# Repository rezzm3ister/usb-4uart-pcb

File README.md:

# usb-4uart-pcb
circuit board for 4x uart board

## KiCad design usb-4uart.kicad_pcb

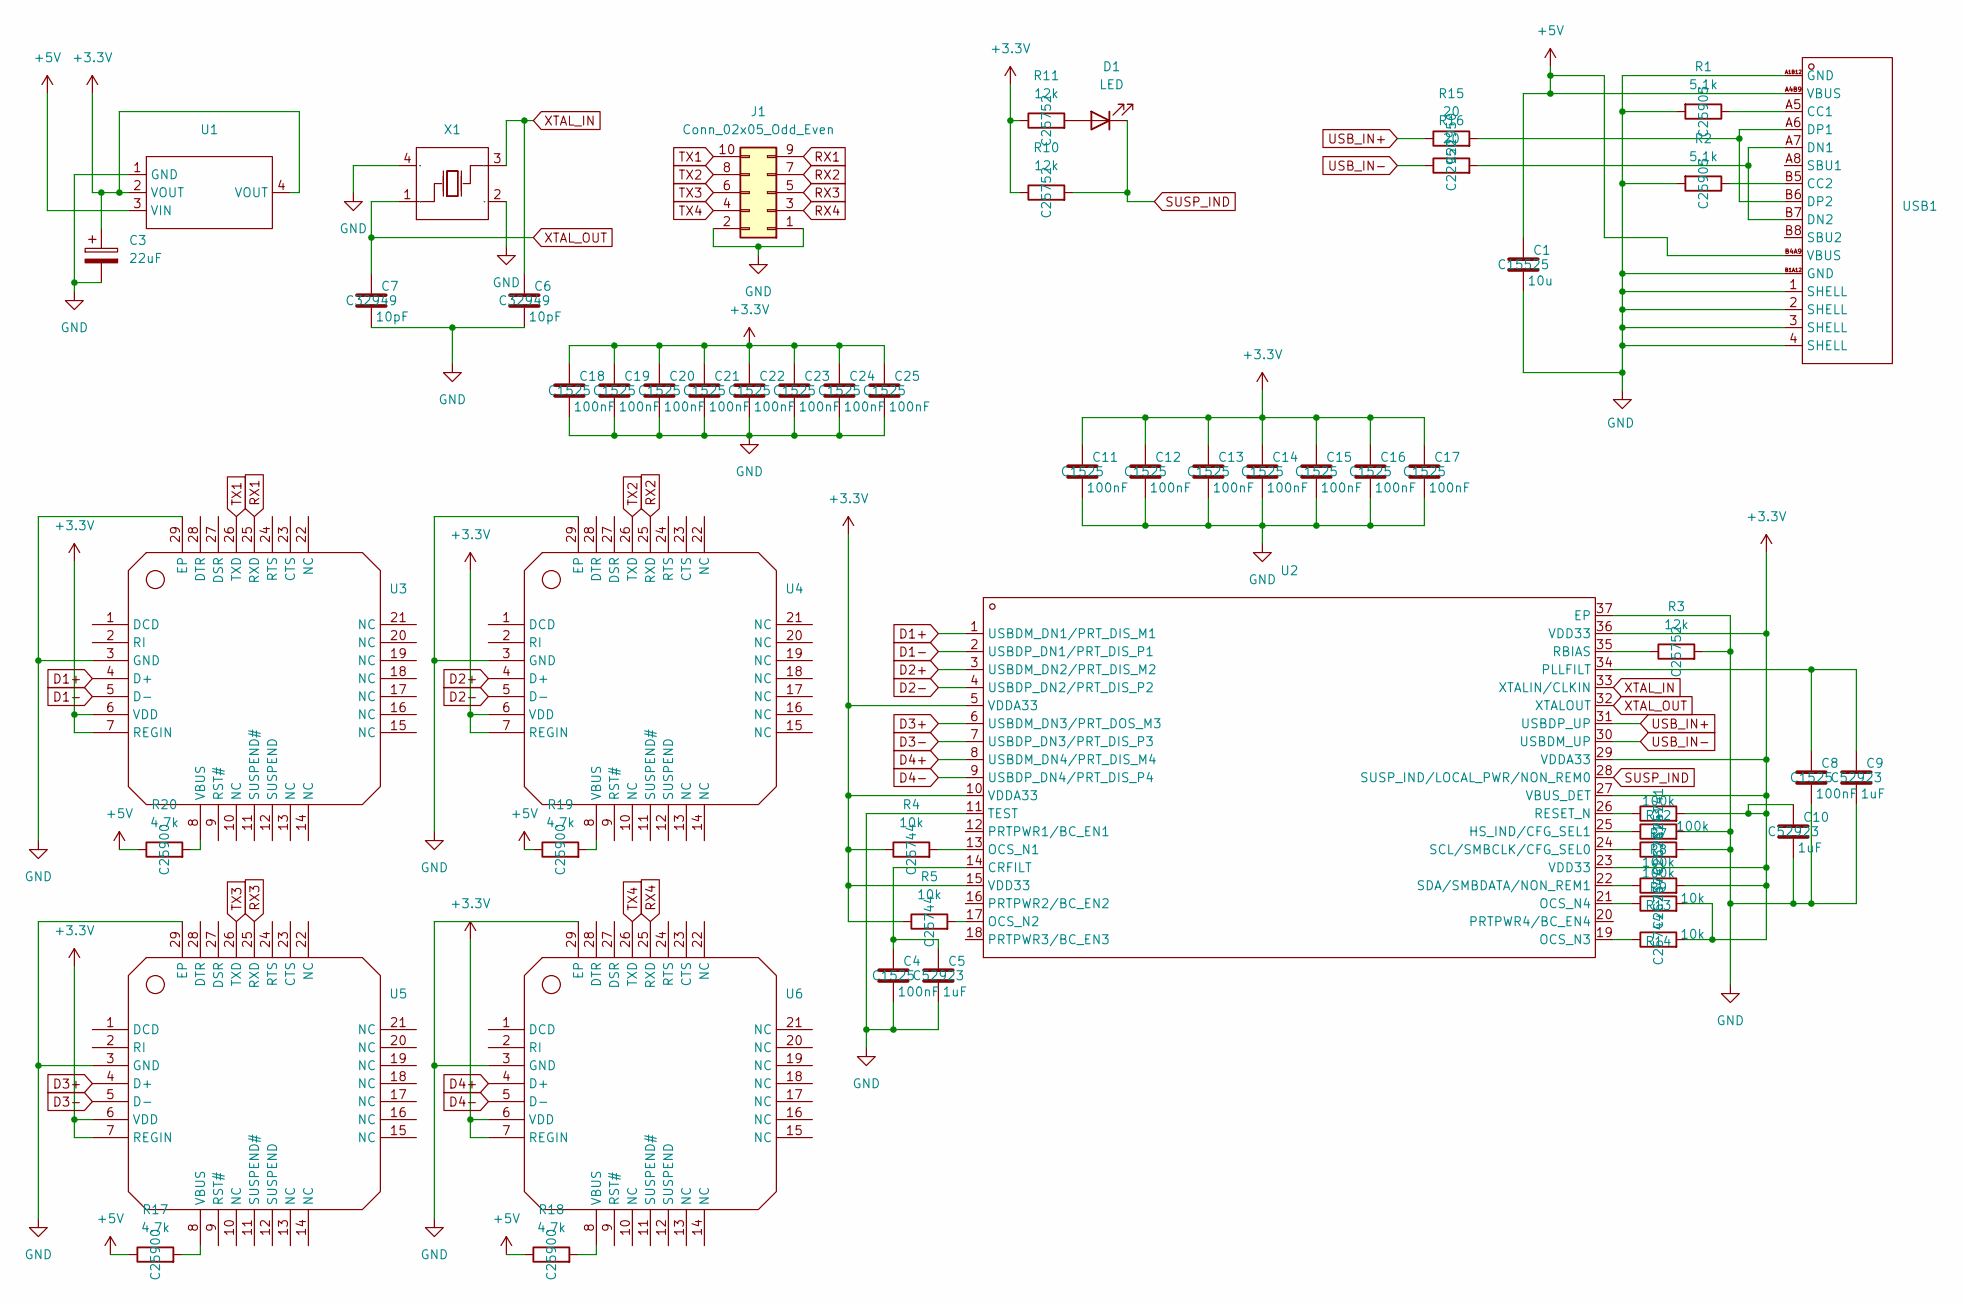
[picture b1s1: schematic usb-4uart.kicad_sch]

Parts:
C1: 10u; C_0603_1608Metric; LCSC C15525
C3: 22uF; CP_EIA-3216-18_Kemet-A; LCSC C7182
C4, C8, C11, C12, C13, C14, C15, C16, C17, C18, C19, C20, C21, C22, C23, C24, C25: 100nF; C_0402_1005Metric; LCSC C1525
C5, C9, C10: 1uF; C_0402_1005Metric; LCSC C52923
C6, C7: 10pF; C_0402_1005Metric; LCSC C32949
D1: LED; LED_0201_0603Metric; LCSC C2286
J1: Conn_02x05_Odd_Even; PinHeader_2x05_P2.54mm_Horizontal; LCSC C60563
R1, R2: 5.1k; R_0402_1005Metric; LCSC C25905
R3, R10, R11: 12k; R_0402_1005Metric; LCSC C25752
R4, R5, R13, R14: 10k; R_0402_1005Metric; LCSC C25744
R7, R8, R9, R12: 100k; R_0402_1005Metric; LCSC C25741
R15, R16: 20; R_0603_1608Metric; LCSC C22950
R17, R18, R19, R20: 4.7k; R_0402_1005Metric; LCSC C25900
U1: AMS1117; Manufacturer Part AMS1117-3.3; LCSC Part Name 输出3.3V 1A
U2: USB2514-VQFN-36_L6.0-W6.0-P0.50-BL-EP; Manufacturer Part USB2514B-AEZC-TR; LCSC Part Name USB 2.0高速集线器控制器
U3, U4, U5, U6: CP2102-WQFN-28_L5.0-W5.0-P0.50-BL-EP3.2; Manufacturer Part CP2102-GMR; LCSC Part Name 单芯片USB转UART桥接器
USB1: USB-C-SMD_TYPE-C16PIN; Manufacturer Part TYPE-C16PIN; LCSC Part Name Type-C 母 卧贴
X1: 24MHz; YXC_24MHz_CRYSTAL; Manufacturer Part X322524MOB4SI; LCSC Part Name 24MHz ±10ppm 12pF

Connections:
+3.3V: C3.1, C10.1, C11.1, C12.1, C13.1, C14.1, C15.1, C16.1, C17.1, C18.1, C19.1, C20.1, C21.1, C22.1, C23.1, C24.1, C25.1, R4.1, R5.1, R9.2, R10.1, R11.1, R12.2, R13.2, R14.2, U1.2 (VOUT), U1.4 (VOUT), U2.5 (VDDA33), U2.10 (VDDA33), U2.15 (VDD33), U2.23 (VDD33), U2.27 (VBUS_DET), U2.29 (VDDA33), U2.36 (VDD33), U3.6 (VDD), U3.7 (REGIN), U4.6 (VDD), U4.7 (REGIN), U5.6 (VDD), U5.7 (REGIN), U6.6 (VDD), U6.7 (REGIN)
+5V: C1.1, R17.1, R18.1, R19.1, R20.1, U1.3 (VIN), USB1.A4B9 (VBUS), USB1.B4A9 (VBUS)
D1+: U2.1 (USBDM_DN1/PRT_DIS_M1), U3.4 (D+)
D1-: U2.2 (USBDP_DN1/PRT_DIS_P1), U3.5 (D-)
D2+: U2.3 (USBDM_DN2/PRT_DIS_M2), U4.4 (D+)
D2-: U2.4 (USBDP_DN2/PRT_DIS_P2), U4.5 (D-)
D3+: U2.6 (USBDM_DN3/PRT_DOS_M3), U5.4 (D+)
D3-: U2.7 (USBDP_DN3/PRT_DIS_P3), U5.5 (D-)
D4+: U2.8 (USBDM_DN4/PRT_DIS_M4), U6.4 (D+)
D4-: U2.9 (USBDP_DN4/PRT_DIS_P4), U6.5 (D-)
GND: C1.2, C3.2, C4.2, C5.2, C6.2, C7.2, C8.2, C9.2, C10.2, C11.2, C12.2, C13.2, C14.2, C15.2, C16.2, C17.2, C18.2, C19.2, C20.2, C21.2, C22.2, C23.2, C24.2, C25.2, J1.1, J1.2, R1.2, R2.2, R3.2, R7.2, R8.2, U1.1 (GND), U2.11 (TEST), U2.37 (EP), U3.3 (GND), U3.29 (EP), U4.3 (GND), U4.29 (EP), U5.3 (GND), U5.29 (EP), U6.3 (GND), U6.29 (EP), USB1.1 (SHELL), USB1.2 (SHELL), USB1.3 (SHELL), USB1.4 (SHELL), USB1.A1B12 (GND), USB1.B1A12 (GND), X1.2 (GND), X1.4 (GND)
unnamed: D1.2 (A), R11.2
unnamed: C4.1, C5.1, U2.14 (CRFILT)
unnamed: R7.1, U2.25 (HS_IND/CFG_SEL1)
unnamed: R4.2, U2.13 (OCS_N1)
unnamed: R5.2, U2.17 (OCS_N2)
unnamed: R14.1, U2.19 (OCS_N3)
unnamed: R13.1, U2.21 (OCS_N4)
unnamed: C8.1, C9.1, U2.34 (PLLFILT)
unnamed: R3.1, U2.35 (RBIAS)
unnamed: R12.1, U2.26 (RESET_N)
unnamed: R8.1, U2.24 (SCL/SMBCLK/CFG_SEL0)
unnamed: R9.1, U2.22 (SDA/SMBDATA/NON_REM1)
unnamed: R20.2, U3.8 (VBUS)
unnamed: R19.2, U4.8 (VBUS)
unnamed: R17.2, U5.8 (VBUS)
unnamed: R18.2, U6.8 (VBUS)
unnamed: R1.1, USB1.A5 (CC1)
unnamed: R2.1, USB1.B5 (CC2)
unnamed: R16.2, USB1.A7 (DN1), USB1.B7 (DN2)
unnamed: R15.2, USB1.A6 (DP1), USB1.B6 (DP2)
RX1: J1.9, U3.25 (RXD)
RX2: J1.7, U4.25 (RXD)
RX3: J1.5, U5.25 (RXD)
RX4: J1.3, U6.25 (RXD)
SUSP_IND: D1.1 (K), R10.2, U2.28 (SUSP_IND/LOCAL_PWR/NON_REM0)
TX1: J1.10, U3.26 (TXD)
TX2: J1.8, U4.26 (TXD)
TX3: J1.6, U5.26 (TXD)
TX4: J1.4, U6.26 (TXD)
USB_IN+: R15.1, U2.31 (USBDP_UP)
USB_IN-: R16.1, U2.30 (USBDM_UP)
XTAL_IN: C6.1, U2.33 (XTALIN/CLKIN), X1.3 (OSC2)
XTAL_OUT: C7.1, U2.32 (XTALOUT), X1.1 (OSC1)

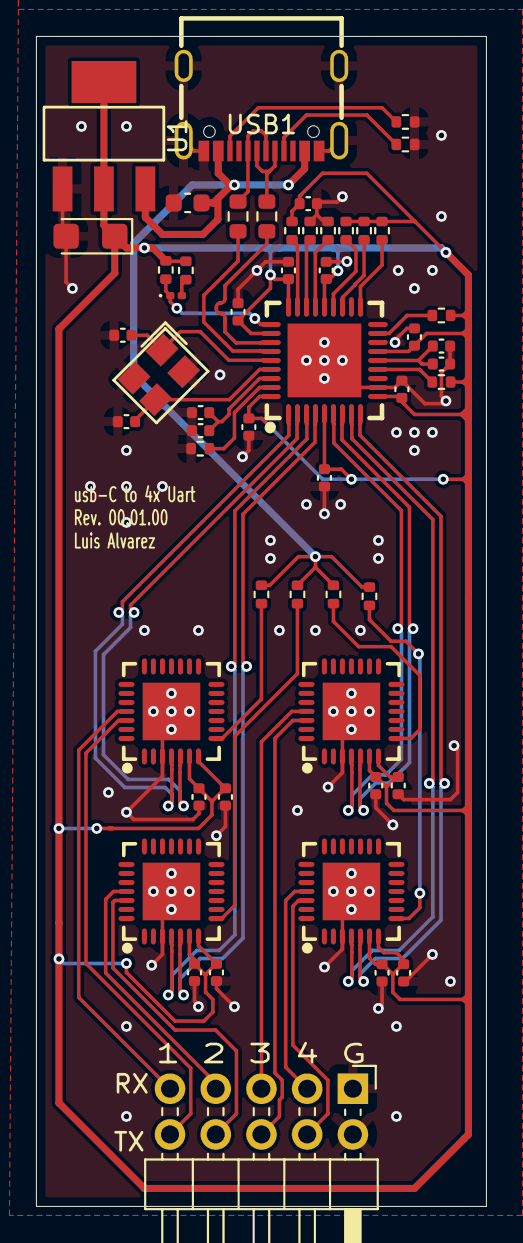
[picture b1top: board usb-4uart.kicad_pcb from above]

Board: 2 copper layers, 25.0 x 65.0 mm, 53 parts (0 on the bottom side), 44 nets.

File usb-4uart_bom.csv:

"Reference","Value","Datasheet","Footprint","Qty","DNP","LCSC","Supplier","Supplier Part"
"C1","10u","~","Capacitor_SMD:C_0603_1608Metric","1","","C15525","",""
"C3","22uF","~","Capacitor_Tantalum_SMD:CP_EIA-3216-18_Kemet-A","1","","C7182","",""
"C4,C8,C11,C12,C13,C14,C15,C16,C17,C18,C19,C20,C21,C22,C23,C24,C25","100nF","~","Capacitor_SMD:C_0402_1005Metric","17","","C1525","",""
"C5,C9,C10","1uF","~","Capacitor_SMD:C_0402_1005Metric","3","","C52923","",""
"C6,C7","10pF","~","Capacitor_SMD:C_0402_1005Metric","2","","C32949","",""
"D1","LED","~","LED_SMD:LED_0201_0603Metric","1",""," C2286","",""
"J1","Conn_02x05_Odd_Even","~","Connector_PinHeader_2.54mm:PinHeader_2x05_P2.54mm_Horizontal","1","","C60563","",""
"R1,R2","5.1k","~","Resistor_SMD:R_0402_1005Metric","2","","C25905","",""
"R3,R10,R11","12k","~","Resistor_SMD:R_0402_1005Metric","3","","C25752","",""
"R4,R5,R13,R14","10k","~","Resistor_SMD:R_0402_1005Metric","4","","C25744","",""
"R7,R8,R9,R12","100k","~","Resistor_SMD:R_0402_1005Metric","4","","C25741","",""
"R15,R16","20","~","Resistor_SMD:R_0603_1608Metric","2","","C22950","",""
"R17,R18,R19,R20","4.7k","~","Resistor_SMD:R_0402_1005Metric","4","","C25900","",""
"U1","~","https://atta.szlcsc.com/upload/public/pdf/source/20180727/C6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","JLCLibrary:AMS1117","1","","C6186","LCSC","C6186"
"U2","~","https://atta.szlcsc.com/upload/public/pdf/source/20130802/14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","JLCLibrary:USB2514-VQFN-36_L6.0-W6.0-P0.50-BL-EP","1","","C16251","LCSC","C16251"
"U3,U4,U5,U6","~","https://atta.szlcsc.com/upload/public/pdf/source/20170103/14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","JLCLibrary:CP2102-WQFN-28_L5.0-W5.0-P0.50-BL-EP3.2","4","","C6568","LCSC","C6568"
"USB1","~","https://atta.szlcsc.com/upload/public/pdf/source/20190521/C3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","JLCLibrary:USB-C-SMD_TYPE-C16PIN","1","","C393939","LCSC","C393939"
"X1","24MHz","https://atta.szlcsc.com/upload/public/pdf/source/20240329/19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","JLCLibrary:YXC_24MHz_CRYSTAL","1","","C70583","LCSC","C70583"

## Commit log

2025-04-23 -updated layout and traces -relocated caps -rotated devices -usb paths more even now
2025-04-25 updated cp2102 vias updated crystal circuitry updated 3v3 joints
2025-04-25 fixed crystal
2025-04-28 -updated to kicad 9.0.1 -reworked layout with correct footprints
2025-04-28 updated a bit
2025-05-10 updated bom and clock
